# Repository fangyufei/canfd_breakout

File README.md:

# canfd_breakout
 
Small footprint can-fd breakout board. Mainly used 0805 smd parts.
Arduino libray acan2517fd works well.

https://github.com/pierremolinaro/acan2517FD

IO Voltage Vio can be set via 0Ohm Resistor R2=>3V3 or R3=>5V.
Even when Vio is set to 3V3, the board (the transceiver) needs 5V supply for proper CAN sending.

The 40MHz crystal can be replaced by a 20MHz or 4MHz crystal. However this affects CAN timing parameters in SW.

PCB:

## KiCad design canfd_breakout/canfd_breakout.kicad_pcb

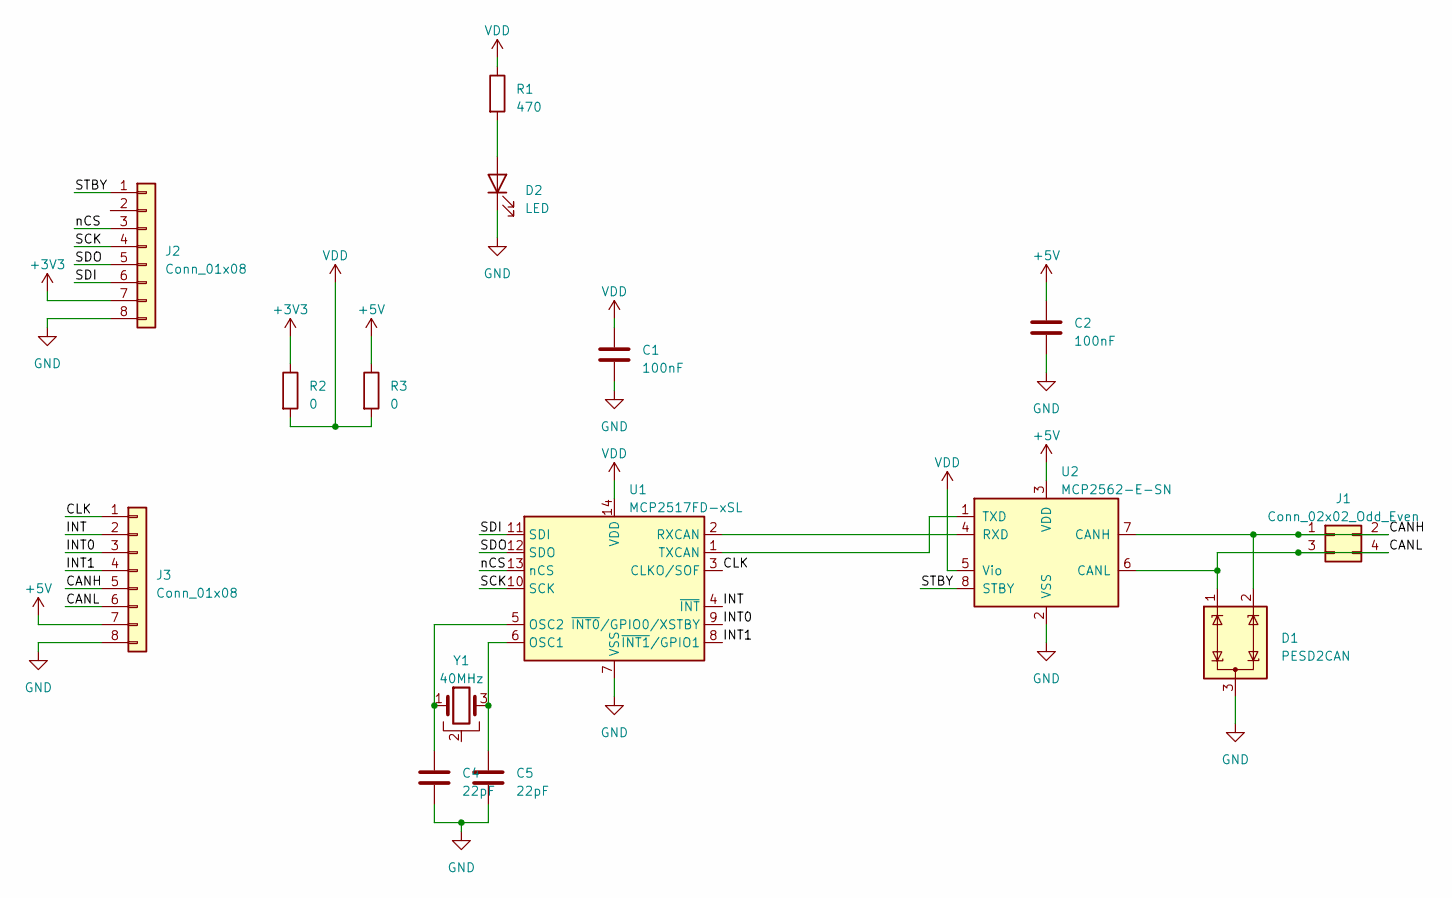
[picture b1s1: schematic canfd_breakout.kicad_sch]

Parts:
C1, C2: 100nF; C_0805_2012Metric_Pad1.18x1.45mm_HandSolder
C4, C5: 22pF; C_0805_2012Metric_Pad1.18x1.45mm_HandSolder
D1: PESD2CAN; SOT-23
D2: LED; LED_0805_2012Metric_Pad1.15x1.40mm_HandSolder
J1: Conn_02x02_Odd_Even; PinHeader_2x02_P2.54mm_Vertical
J2, J3: Conn_01x08; PinHeader_1x08_P2.54mm_Vertical
R1: 470; C_0805_2012Metric_Pad1.18x1.45mm_HandSolder
R2, R3: 0; R_0805_2012Metric_Pad1.20x1.40mm_HandSolder
U1: MCP2517FD-xSL; SOIC-14_3.9x8.7mm_P1.27mm
U2: MCP2562-E-SN; SOIC-8_3.9x4.9mm_P1.27mm
Y1: 40MHz; Crystal_SMD_3225-4Pin_3.2x2.5mm

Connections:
+3V3: J2.7, R2.1
+5V: C2.1, J3.7, R3.1, U2.3 (VDD)
/CANH: D1.2 (K), J1.1, J1.2, J3.5, U2.7 (CANH)
/CANL: D1.1 (K), J1.3, J1.4, J3.6, U2.6 (CANL)
/CLK: J3.1, U1.3 (CLKO/SOF)
/INT: J3.2, U1.4 (~INT)
/INT0: J3.3, U1.9 (~INT0/GPIO0/XSTBY)
/INT1: J3.4, U1.8 (~INT1/GPIO1)
/SCK: J2.4, U1.10 (SCK)
/SDI: J2.6, U1.11 (SDI)
/SDO: J2.5, U1.12 (SDO)
/STBY: J2.1, U2.8 (STBY)
/nCS: J2.3, U1.13 (nCS)
GND: C1.2, C2.2, C4.2, C5.2, D1.3 (A), D2.1 (K), J2.8, J3.8, U1.7 (VSS), U2.2 (VSS)
unnamed: D2.2 (A), R1.2
unnamed: C5.1, U1.6 (OSC1), Y1.3
unnamed: C4.1, U1.5 (OSC2), Y1.1
unnamed: U1.2 (RXCAN), U2.4 (RXD)
unnamed: U1.1 (TXCAN), U2.1 (TXD)
VDD: C1.1, R1.1, R2.2, R3.2, U1.14 (VDD), U2.5 (Vio)

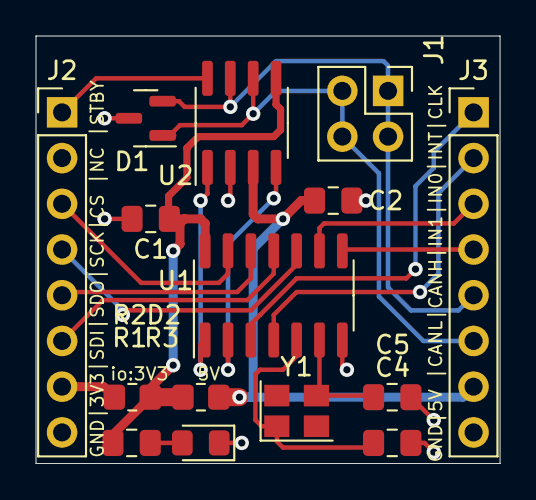
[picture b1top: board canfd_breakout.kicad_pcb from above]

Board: 2 copper layers, 25.8 x 23.7 mm, 15 parts (0 on the bottom side), 20 nets.

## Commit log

2023-11-16 add pdf shematic
2023-12-22 correct CAN high low label
